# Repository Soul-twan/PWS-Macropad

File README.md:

Code and files I wrote for a school research project.

This project uses a Raspberry Pi Pico 2 family microcontroller to make a reprogrammable macropad. The microncontroller code is based on code from the Adafruit TinyUSB Library for Arduino (https://github.com/adafruit/Adafruit_TinyUSB_Arduino/blob/master/examples/HID/hid_composite/hid_composite.ino).

Microcontroller setup guide:
-

  1. Connect the microcontroller to your computer as a mass storage device by holding the button labelled "Bootsel" while plugging the USB-connector into your computer, it should show up as "RP2350"
  2. Download the latest release of the microcontroller code 
  3. Extract the downloaded "Microcontroller.code.zip" file 
  4. Move the folder labelled "Microcontroller code" over to the root of the Pico. Be sure to move the entire folder, not just its contents

If done properly, the Pico should disconnect automatically after moving over the folder.

PCB:
-
PCB designed with KiCad 9.0 and should work with PCB ordering services such as PCBWay.

Code compilation guide:
-

  1. Download the Arduino IDE
  2. Open MicrocontrollerCode.ino in the IDE
  3. In the menubar go to File > Preferences > Settings and add "https://github.com/earlephilhower/arduino-pico/releases/download/global/package_rp2040_index.json" to the Additional boards manager URLs
  4. In the boards manager in the sidebar install "Raspberry Pi Pico/RP2040/RP2350" by Earle F. Philhower, |||
  5. In the library manager in the sidebar install "Adafruit TinyUSB Library" by Adafruit
  6. In the dropdown below the menubar press "Select other boards and port...", then select the USB port that the raspberry pi is connected to and search and select the correct Raspberry Pi Pico model
  7. In the menubar go to Tools > USB Stack and select Adafruit TinyUSB\
  8. Press upload

If done properly, the code should be compiled and automatically uploaded to the microcontroller

Standard keymaps:
-

Encoders:
 1. Press: switch keymap, Turn: change screen brightness
 2. Press: mute volume, Turn: change volume

Keymap 1:  Sends signals to the companion app

  1. F13
  2. F14
  3. F15
  4. F16
  5. F17
  6. F18
  7. F19
  8. F20
  9. F21
  10. F22
  11. F23
  12. F24

Keymap 2: Mouse

 1. Left click
 2. Middle click
 3. Right click
 4. Scroll up
 5. Move mouse up
 6. Scroll down
 7. Move mouse left
 8. Scroll lock
 9. Move mouse right
 10. Scroll left
 11. Move mouse down
 12. Scroll right

Keymap 3: Various shortcuts

 1. Previous track
 2. Next track
 3. Play/pause
 4. Ctrl + x
 5. Ctrl + c
 6. Ctrl + v
 7. Ctrl + z
 8. Ctrl + s
 9. Alt + tab
 10. Calculator
 11. Screenshot
 12. Delete

Components:
- 
Off the shelf:
 - PEC12R-4217F-S0024 rotary encoder
 - Kaihl hotswap sockets for cherry mx
 - Cherry MX keyswitches
 - Raspberry Pi Pico 2 + socket
 - Keycaps for cherry mx (optional)

Custom:
 - PCB
 - 3d printed case
 - 3d printed knobs
 - 3d printed keycaps

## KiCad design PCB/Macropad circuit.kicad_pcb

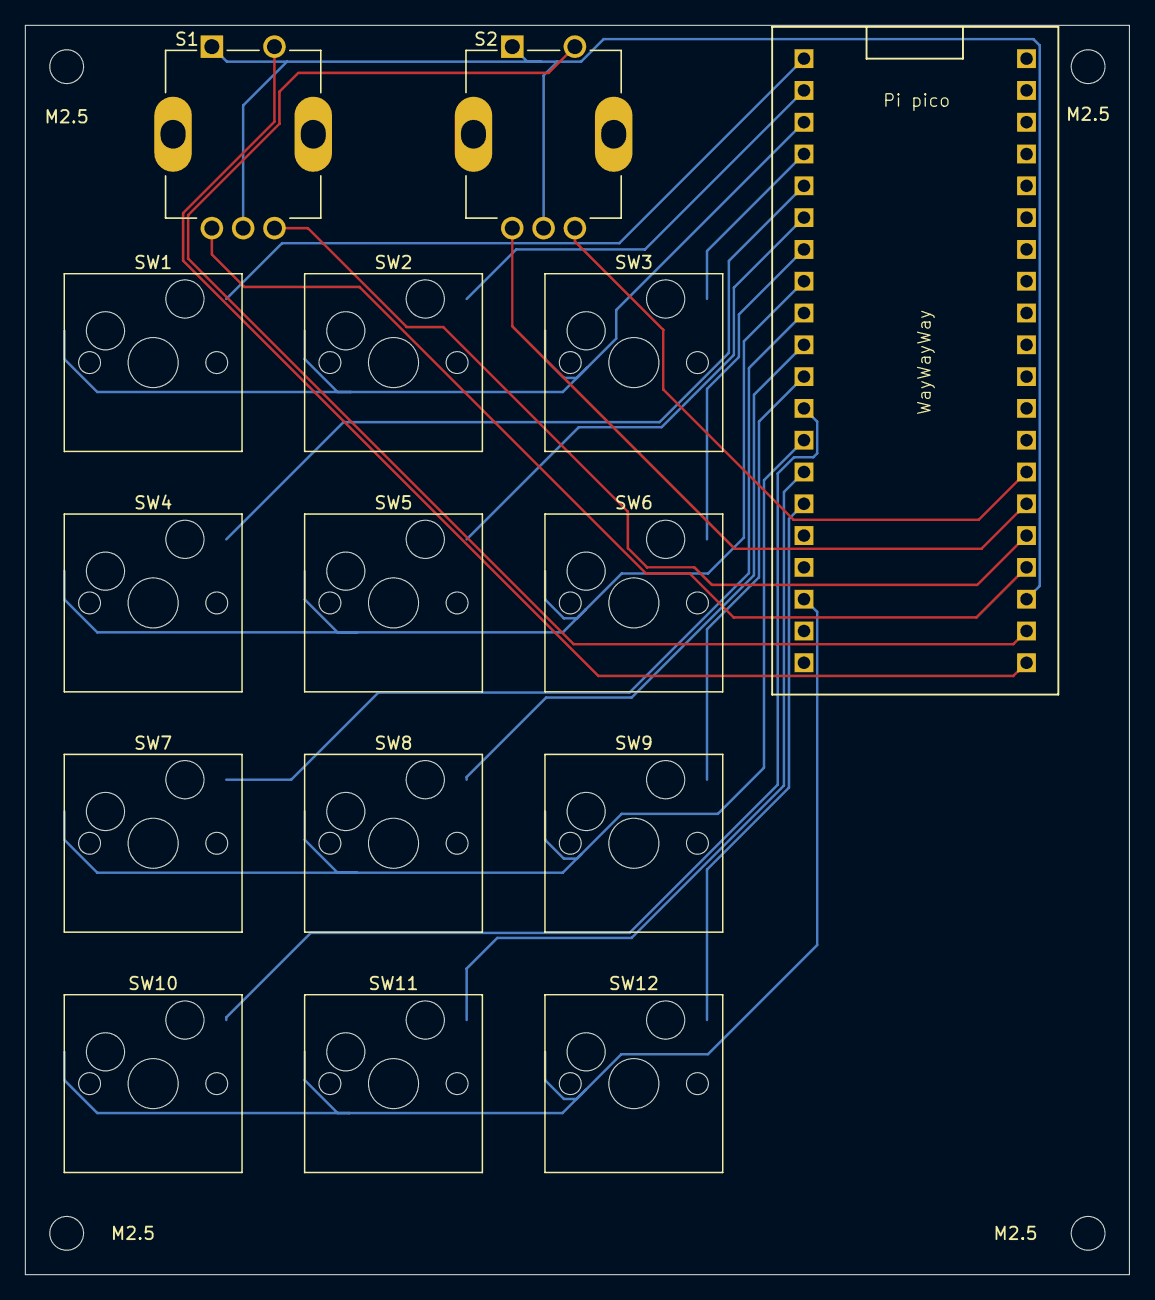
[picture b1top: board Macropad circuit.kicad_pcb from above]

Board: 2 copper layers, 88.2 x 99.8 mm, 19 parts (0 on the bottom side), 23 nets.

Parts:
M2.5, M2.5#2, M2.5#3, M2.5#4: MountingHole_2.7mm_M2.5
Pi pico: Raspberrypi pico2 THT
S1, S2: PEC12R-4230F-S0024; XDCR_PEC12R-4230F-S0024
SW1, SW2, SW3, SW4, SW5, SW6, SW7, SW8, SW9, SW10, SW11, SW12: CherryMX; SW_Hotswap_Kailh_MX_1.00u

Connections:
Button1: Pi pico.GP0, SW1.2
Button2: Pi pico.GP1, SW2.2
Button3: Pi pico.GP2, SW3.2
Button4: Pi pico.GP3, SW4.2
Button5: Pi pico.GP4, SW5.2
Button6: Pi pico.GP5, SW6.2
Button7: Pi pico.GP6, SW7.2
Button8: Pi pico.GP7, SW8.2
Button9: Pi pico.GP8, SW9.2
Button10: Pi pico.GP9, SW10.2
Button11: Pi pico.GP10, SW11.2
Button12: Pi pico.GP11, SW12.2
EncoderButton1: Pi pico.GP16, S1.2
EncoderButton2: Pi pico.GP17, S2.2
EncoderChannel1: Pi pico.GP18, S1.A (CHANNEL_A)
EncoderChannel2: Pi pico.GP19, S1.B (CHANNEL_B)
EncoderChannel3: Pi pico.GP20, S2.A (CHANNEL_A)
EncoderChannel4: Pi pico.GP21, S2.B (CHANNEL_B)
EncoderGround: Pi pico.GND, S1.1, S1.C (COMMON), S2.1, S2.C (COMMON)
GroundButtonRow1: Pi pico.GND, SW1.1, SW2.1, SW3.1
GroundButtonRow2: Pi pico.GND, SW4.1, SW5.1, SW6.1
GroundButtonRow3: Pi pico.GND, SW7.1, SW8.1, SW9.1
GroundButtonRow4: Pi pico.GND, SW10.1, SW11.1, SW12.1

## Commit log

2025-07-24 Update LICENSE
    Updated copyright names
2025-07-24 Create README.md
    Created and wrote read me file
2025-07-24 Update README.md
    Added link and explanation to the code which the microcontroller code is based on
2025-07-24 Added firts basics of microcontroller code
2025-07-24 Update MicrocontrollerCode.ino
    Added functionality
2025-07-26 Update MicrocontrollerCode.ino
    Fixed license and massively improved functionality and modularity
2025-07-28 Update MicrocontrollerCode.ino
    Cleaned up code and added scrolling
2025-07-29 Update MicrocontrollerCode.ino
    Fixed bugs and added keymap switching
2025-08-22 Update MicrocontrollerCode.ino
    Added rotary encoders and optimized a bit
2025-08-23 Update MicrocontrollerCode.ino
    Improved encoder performance and organized functions
2025-08-23 Update MicrocontrollerCode.ino
    Switched out standard shortcuts and proved myself wrong (turned assigning keys in the array into a for loop)
2025-09-07 Update README.md
    Added a microcontroller setup guide
2025-09-07 Update README.md
    Fixed spacing
2025-09-09 Update MicrocontrollerCode.ino
    Changed standard shortcuts and updated for new tinyusb library version
2025-09-24 Added PCB schematics
2025-10-16 Update MicrocontrollerCode.ino
    Changed standard shortcuts to be a better example and added some commentary
2025-11-16 Update MicrocontrollerCode.ino
    Added commentary for the keymap to make it easier to change by a user
2025-11-16 Update README.md
    Added standard keymap descriptions
2025-11-16 Update README.md
    Added headers and component list
2025-11-23 Added case model
    Case, knobs and keycaps model design file
2025-11-23 Update README.md
    Added compile instructions
2025-11-23 Update README.md
    Fixed a spelling error
